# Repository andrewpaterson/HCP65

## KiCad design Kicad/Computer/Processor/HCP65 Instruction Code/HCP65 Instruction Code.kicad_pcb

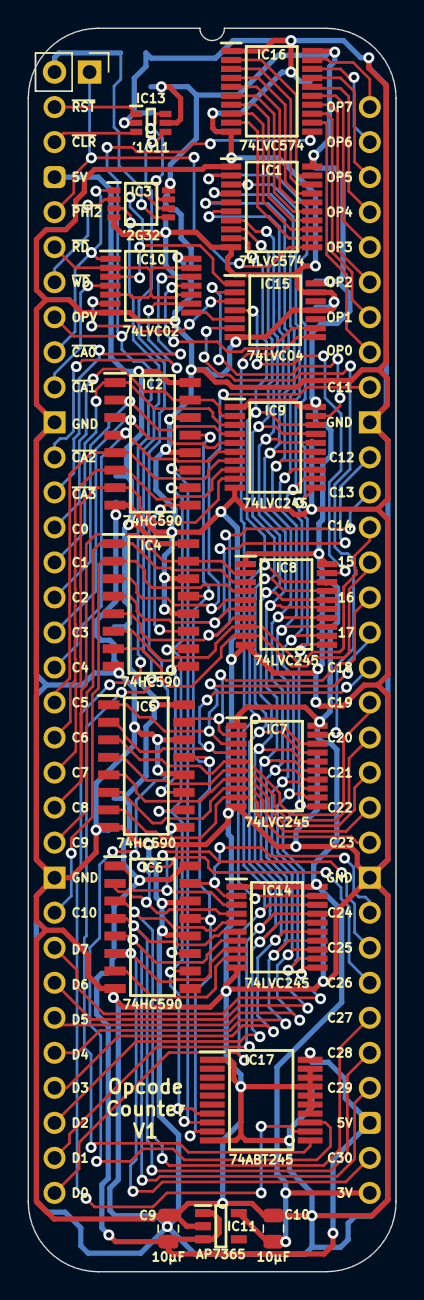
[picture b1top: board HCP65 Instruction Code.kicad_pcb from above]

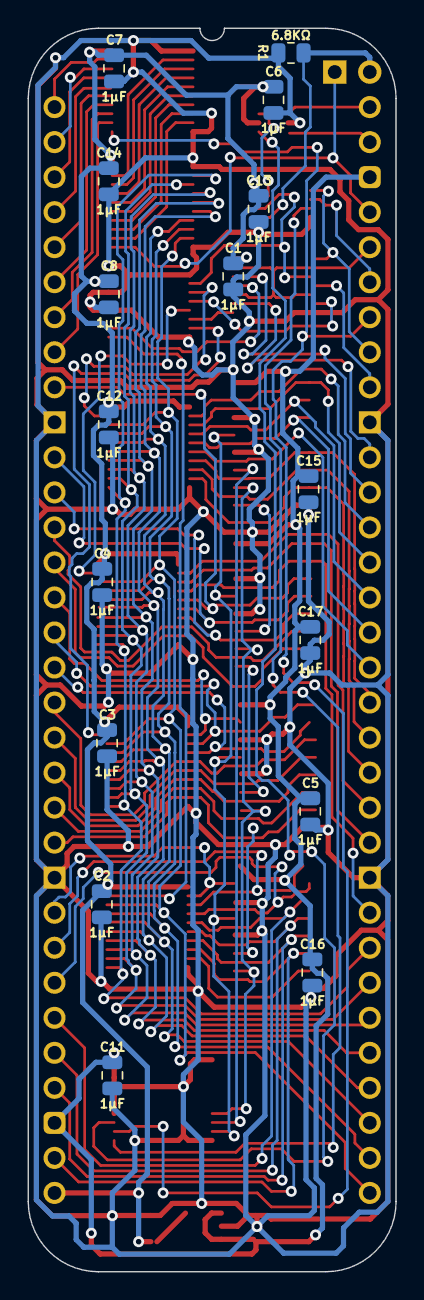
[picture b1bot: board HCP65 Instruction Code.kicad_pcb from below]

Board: 2 copper layers, 26.7 x 90.2 mm, 36 parts (16 on the bottom side), 87 nets.

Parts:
C1, C2, C3, C4, C5, C6, C7, C8, C11, C12, C13, C14, C15, C16, C17: 1μF; C_0805
C9, C10: 10μF; C_0805
IC1, IC16: 74LVC574APW,118; SOP65P640X110-20N
IC2, IC4, IC5, IC6: 74HC590D,118; SOIC127P600X175-16N
IC3: 74LVC2G32DP,125; SOP65P400X110-8N
IC7, IC8, IC9, IC14: 74LVC245AT20; SOP65P640X120-20N
IC10: 74LVC02APW,118; SOP65P640X110-14N
IC11: AP7365-33WG-7; SOT95P285X130-5N
IC13: 74LVC1G11GW-Q100H; SOP65P210X110-6N
IC15: 74LVC04APW,118; SOP65P640X110-14N
IC17: SN74ABT245BDBR; SOP65P780X200-20N
J2: Board 2x32 W22.86mm; DIP-64_Board_W22.86mm
J4: Conn_01x02_Pin; PinHeader_1x02_P2.54mm_Vertical
R1: 6.8KΩ; R_0805

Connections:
3.3V: C1.2, C2.2, C3.2, C4.2, C6.2, C7.2, C8.2, C10.1, C12.2, C13.2, C14.2, IC1.20 (3V), IC3.8 (VCC), IC7.1 (DIR), IC7.20 (3V), IC8.1 (DIR), IC8.20 (3V), IC9.1 (DIR), IC9.20 (3V), IC10.14 (3V), IC11.5 (3.3VOut), IC13.5 (3V), IC14.1 (DIR), IC14.20 (3V), IC15.14 (3V), IC16.20 (3V), J2.33
5V: C5.2, C9.1, C11.2, C15.2, C16.2, C17.2, IC2.16 (VCC), IC4.16 (VCC), IC5.16 (VCC), IC6.16 (VCC), IC11.1 (6VIn), IC11.3 (EN), IC17.20 (5V), J2.3, J2.35
/C31: IC6.7 (Q7), IC14.9 (A7)
/Opcode Valid_{5V}: IC2.11 (CPC), IC17.8 (A6)
/Q0: IC1.19 (Q0), IC16.2 (D0)
/Q1: IC1.18 (Q1), IC16.3 (D1)
/Q2: IC1.17 (Q2), IC16.4 (D2)
/Q3: IC1.16 (Q3), IC16.5 (D3)
/Q4: IC1.15 (Q4), IC16.6 (D4)
/Q5: IC1.14 (Q5), IC16.7 (D5)
/Q6: IC1.13 (Q6), IC16.8 (D6)
/Q7: IC1.12 (Q7), IC16.9 (D7)
/Read Count Access_{0T}: IC3.6 (2B), IC10.3 (1Y), IC15.1 (1A)
/Read Count Access_{0}: IC3.3 (2Y), IC17.11 (B7)
/Read Count Access_{1}: IC10.6 (2Y), IC15.3 (2A)
/Read Count Access_{2}: IC10.8 (3Y), IC15.5 (3A)
/Read Count Access_{3}: IC10.11 (4Y), IC15.9 (4A)
/Read Count_{5V}: IC2.13 (CPR), IC4.13 (CPR), IC5.13 (CPR), IC6.13 (CPR), IC17.9 (A7)
/~MRC: IC13.4 (Y), IC17.13 (B5)
/~MRC_{5V}: IC2.10 (~MRC), IC4.10 (~MRC), IC5.10 (~MRC), IC6.10 (~MRC), IC17.7 (A5)
/~Read Count Access_{0}: IC9.19 (~OE), IC15.2 (1Y)
/~Read Count Access_{1}: IC8.19 (~OE), IC15.4 (2Y)
/~Read Count Access_{2}: IC7.19 (~OE), IC15.6 (3Y)
/~Read Count Access_{3}: IC14.19 (~OE), IC15.8 (4Y)
/~Write Count: IC3.7 (1Y), IC13.6 (C)
C0: IC2.15 (Q0), IC9.2 (A0), J2.13
C1: IC2.1 (Q1), IC9.3 (A1), J2.14
C2: IC2.2 (Q2), IC9.4 (A2), J2.15
C3: IC2.3 (Q3), IC9.5 (A3), J2.16
C4: IC2.4 (Q4), IC9.6 (A4), J2.17
C5: IC2.5 (Q5), IC9.7 (A5), J2.18
C6: IC2.6 (Q6), IC9.8 (A6), J2.19
C7: IC2.7 (Q7), IC9.9 (A7), J2.20
C8: IC4.15 (Q0), IC8.2 (A0), J2.21
C9: IC4.1 (Q1), IC8.3 (A1), J2.22
C10: IC4.2 (Q2), IC8.4 (A2), J2.24
C11: IC4.3 (Q3), IC8.5 (A3), J2.56
C12: IC4.4 (Q4), IC8.6 (A4), J2.54
C13: IC4.5 (Q5), IC8.7 (A5), J2.53
C14: IC4.6 (Q6), IC8.8 (A6), J2.52
C15: IC4.7 (Q7), IC8.9 (A7), J2.51
C16: IC5.15 (Q0), IC7.2 (A0), J2.50
C17: IC5.1 (Q1), IC7.3 (A1), J2.49
C18: IC5.2 (Q2), IC7.4 (A2), J2.48
C19: IC5.3 (Q3), IC7.5 (A3), J2.47
C20: IC5.4 (Q4), IC7.6 (A4), J2.46
C21: IC5.5 (Q5), IC7.7 (A5), J2.45
C22: IC5.6 (Q6), IC7.8 (A6), J2.44
C23: IC5.7 (Q7), IC7.9 (A7), J2.43
C24: IC6.15 (Q0), IC14.2 (A0), J2.41
C25: IC6.1 (Q1), IC14.3 (A1), J2.40
C26: IC6.2 (Q2), IC14.4 (A2), J2.39
C27: IC6.3 (Q3), IC14.5 (A3), J2.38
C28: IC6.4 (Q4), IC14.6 (A4), J2.37
C29: IC6.5 (Q5), IC14.7 (A5), J2.36
C30: IC6.6 (Q6), IC14.8 (A6), J2.34
D0: IC1.9 (D7), IC7.18 (B0), IC8.18 (B0), IC9.18 (B0), IC14.18 (B0), J2.32
D1: IC1.8 (D6), IC7.17 (B1), IC8.17 (B1), IC9.17 (B1), IC14.17 (B1), J2.31
D2: IC1.7 (D5), IC7.16 (B2), IC8.16 (B2), IC9.16 (B2), IC14.16 (B2), J2.30
D3: IC1.6 (D4), IC7.15 (B3), IC8.15 (B3), IC9.15 (B3), IC14.15 (B3), J2.29
D4: IC1.5 (D3), IC7.14 (B4), IC8.14 (B4), IC9.14 (B4), IC14.14 (B4), J2.28
D5: IC1.4 (D2), IC7.13 (B5), IC8.13 (B5), IC9.13 (B5), IC14.13 (B5), J2.27
D6: IC1.3 (D1), IC7.12 (B6), IC8.12 (B6), IC9.12 (B6), IC14.12 (B6), J2.26
D7: IC1.2 (D0), IC7.11 (B7), IC8.11 (B7), IC9.11 (B7), IC14.11 (B7), J2.25
GND: C1.1, C2.1, C3.1, C4.1, C5.1, C6.1, C7.1, C8.1, C9.2, C10.2, C11.1, C12.1, C13.1, C14.1, C15.1, C16.1, C17.1, IC1.1 (~OE), IC1.10 (GND), IC2.8 (GND), IC2.12 (~CE), IC2.14 (~OE), IC3.4 (GND), IC4.8 (GND), IC4.12 (~CE), IC4.14 (~OE), IC5.8 (GND), IC5.12 (~CE), IC5.14 (~OE), IC6.8 (GND), IC6.12 (~CE), IC6.14 (~OE), IC7.10 (GND), IC8.10 (GND), IC9.10 (GND), IC10.7 (GND), IC11.2 (GND), IC13.2 (GND), IC14.10 (GND), IC15.7 (GND), IC15.11 (5A), IC15.13 (6A), IC16.1 (~OE), IC16.10 (GND), IC17.1 (DIR), IC17.10 (GND), IC17.14 (B4), IC17.15 (B3), IC17.16 (B2), IC17.17 (B1), IC17.18 (B0), IC17.19 (~OE), J2.10, J2.23, J2.42, J2.55, R1.2
unnamed: IC2.9 (~RCO), IC4.11 (CPC)
unnamed: IC3.5 (2A), J4.2, R1.1
unnamed: IC4.9 (~RCO), IC5.11 (CPC)
unnamed: IC5.9 (~RCO), IC6.11 (CPC)
OP0: IC16.12 (Q7), J2.57
OP1: IC16.13 (Q6), J2.58
OP2: IC16.14 (Q5), J2.59
OP3: IC16.15 (Q4), J2.60
OP4: IC16.16 (Q3), J2.61
OP5: IC16.17 (Q2), J2.62
OP6: IC16.18 (Q1), J2.63
OP7: IC16.19 (Q0), J2.64
Opcode Valid: IC16.11 (CP), IC17.12 (B6), J2.7
~Clear Counter: IC13.3 (B), J2.2
~Count Access_{0}: IC3.1 (1A), IC10.1 (1A), J2.8
~Count Access_{1}: IC10.4 (2A), J2.9
~Count Access_{2}: IC10.9 (3A), J2.11
~Count Access_{3}: IC10.12 (4A), J2.12
~PHI2: IC1.11 (CP), J2.4, J4.1
~RD: IC10.2 (1B), IC10.5 (2B), IC10.10 (3B), IC10.13 (4B), J2.5
~Reset: IC13.1 (A), J2.1
~WD: IC3.2 (1B), J2.6

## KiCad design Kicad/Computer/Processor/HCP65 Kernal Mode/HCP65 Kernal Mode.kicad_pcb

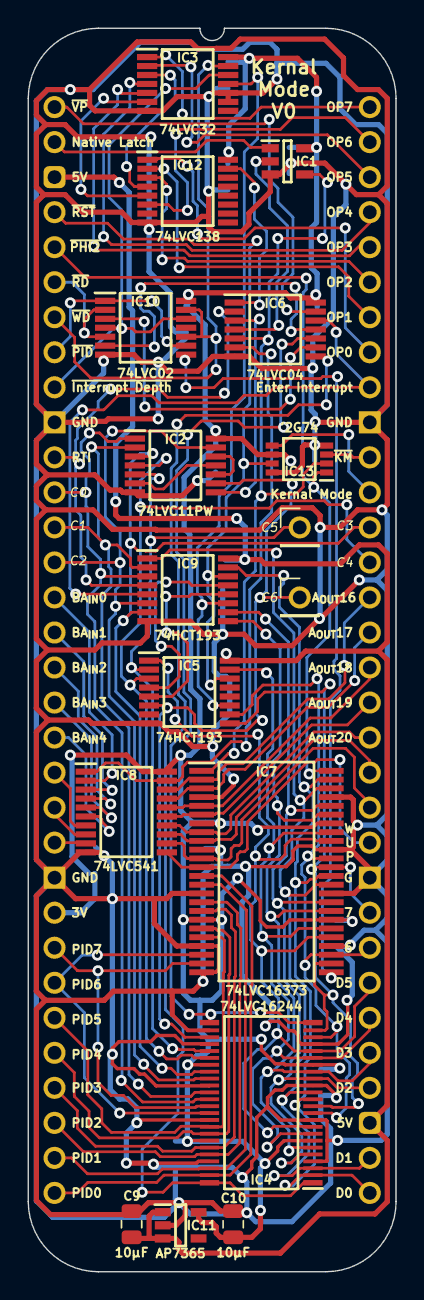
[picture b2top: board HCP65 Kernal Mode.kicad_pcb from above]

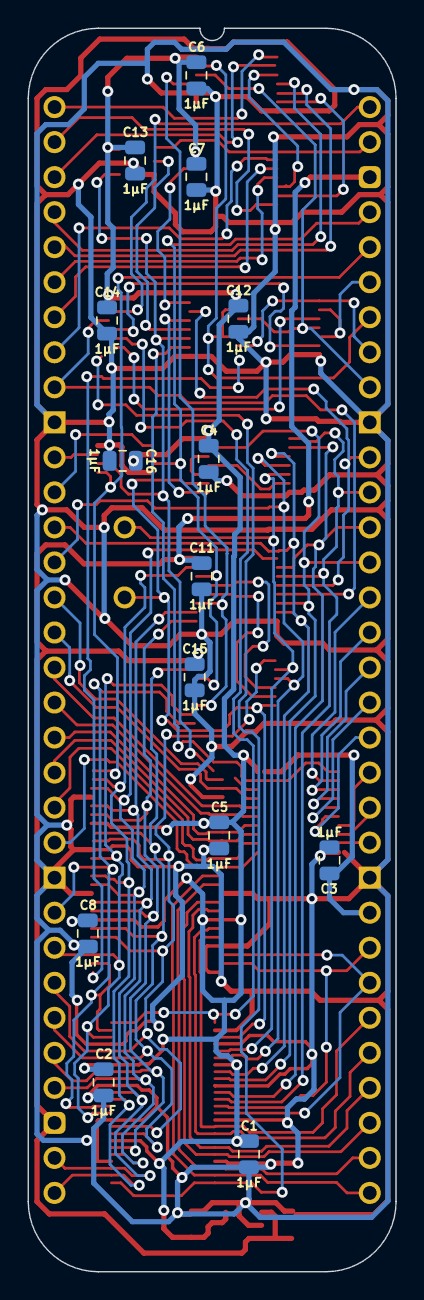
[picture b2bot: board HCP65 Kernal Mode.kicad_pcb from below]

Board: 2 copper layers, 26.7 x 90.2 mm, 32 parts (14 on the bottom side), 79 nets.

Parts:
C1, C2, C3, C4, C5, C6, C7, C8, C11, C12, C13, C14, C15, C16: 1μF; C_0805
C9, C10: 10μF; C_0805
IC1: 74LVC1G02GV,125; SOT95P275X110-5N
IC2: 74LVC11PW,112; SOP65P640X110-14N
IC3: 74LVC32APW,118; SOP65P640X110-14N
IC4: 74LVC16244ADGG,112; 74LVC16244ADGG112
IC5, IC9: 74HCT193PW,118; SOP65P640X110-16N
IC6: 74LVC04APW,118; SOP65P640X110-14N
IC7: 74LVC16373ADL,118; SOP64P1025X280-48N
IC8: 74LVC541APW,118; SOP65P640X110-20N
IC10: 74LVC02APW,118; SOP65P640X110-14N
IC11: AP7365-33WG-7; SOT95P285X130-5N
IC12: 74LVC138APW-Q100J; SOP65P640X110-16N
IC13: 74LVC2G74DP,125; SOP65P400X110-8N
J2: Board 2x32 W22.86mm; DIP-64_Board_W22.86mm
TP1, TP2: TestPoint; PinHeader_1x01_P2.54mm_Vertical

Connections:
3.3V: C1.2, C2.2, C3.2, C4.2, C5.2, C6.2, C7.2, C8.2, C10.1, C12.2, C13.2, C14.2, C16.2, IC1.5 (3V), IC2.14 (3V), IC3.14 (3V), IC4.7 (3V), IC4.18 (3V), IC4.31 (3V), IC4.42 (3V), IC6.14 (3V), IC7.7 (3V), IC7.18 (3V), IC7.31 (3V), IC7.42 (3V), IC8.20 (3V), IC10.14 (3V), IC11.5 (3.3VOut), IC12.16 (3V), IC13.6 (~RD), J2.24
5V: C9.1, C11.2, C15.2, IC5.16 (5V), IC9.16 (5V), IC11.1 (6VIn), IC11.3 (EN), J2.3, J2.35
/C0·C1·C2: IC2.10 (3B), IC2.12 (1Y)
/C3·C4·C5: IC2.6 (2Y), IC2.11 (3C)
/Kernal Mode: IC1.4 (Y), IC6.5 (3A), IC7.1 (1~OE), IC13.2 (D)
/Kernal Mode_{ PART}: IC2.8 (3Y), IC6.3 (2A)
/OP3+OP4: IC3.6 (2Y), IC12.5 (~E2)
/OP5+OP7: IC3.3 (1Y), IC12.4 (~E1)
/Read Interrupt Depth: IC6.11 (5A), IC10.6 (2Y)
/Read Process ID: IC6.9 (4A), IC10.3 (1Y)
/Write Process ID: IC7.25 (2LE), IC10.8 (3Y)
/~Kernal Mode: IC6.6 (3Y), IC8.1 (~OE1), IC8.19 (~OE2)
/~Kernal Mode_{ PART}: IC1.2 (A), IC6.4 (2Y)
/~RTI: IC6.1 (1A), IC12.15 (~Y0)
/~Read Interrupt Depth: IC4.24 (4~OE), IC4.25 (3~OE), IC6.10 (5Y)
/~Read Process ID: IC4.1 (1~OE), IC4.48 (2~OE), IC6.8 (4Y)
/~TCD: IC5.4 (CPD), IC9.13 (~TCD)
/~TCU: IC5.5 (CPU), IC9.12 (~TCU)
/~Write Interrupt Depth: IC3.11 (4Y), IC5.11 (~PL), IC9.11 (~PL)
A_{OUT}16: IC7.2 (1Q0), IC8.18 (Y0), J2.50
A_{OUT}17: IC7.3 (1Q1), IC8.17 (Y1), J2.49
A_{OUT}18: IC7.5 (1Q2), IC8.16 (Y2), J2.48
A_{OUT}19: IC7.6 (1Q3), IC8.15 (Y3), J2.47
A_{OUT}20: IC7.8 (1Q4), IC8.14 (Y4), J2.46
A_{OUT}21: IC7.9 (1Q5), IC8.13 (Y5), J2.45
A_{OUT}22: IC7.11 (1Q6), IC8.12 (Y6), J2.44
A_{OUT}23: IC7.12 (1Q7), IC8.11 (Y7), J2.43
BA_{IN}0: IC8.2 (A0), J2.15
BA_{IN}1: IC8.3 (A1), J2.16
BA_{IN}2: IC8.4 (A2), J2.17
BA_{IN}3: IC8.5 (A3), J2.18
BA_{IN}4: IC8.6 (A4), J2.19
BA_{IN}5: IC8.7 (A5), J2.20
BA_{IN}6: IC8.8 (A6), J2.21
BA_{IN}7: IC8.9 (A7), J2.22
C0: IC2.1 (1A), IC4.36 (3A0), IC9.3 (Q0), J2.12
C1: IC2.2 (1B), IC4.35 (3A1), IC9.2 (Q1), J2.13
C2: IC2.13 (1C), IC4.33 (3A2), IC9.6 (Q2), J2.14
C3: IC2.3 (2A), IC4.32 (3A3), IC9.7 (Q3), J2.52
C4: IC2.4 (2B), IC4.30 (4A0), IC5.3 (Q0), J2.51
C5: IC2.5 (2C), IC4.29 (4A1), IC5.2 (Q1), TP2.1 (1_1)
C6: IC2.9 (3A), IC4.27 (4A2), IC5.6 (Q2), TP1.1 (1_1)
D0: IC4.2 (1Y0), IC4.13 (3Y0), IC7.36 (2D0), IC7.47 (1D0), IC9.15 (D0), J2.33
D1: IC4.3 (1Y1), IC4.14 (3Y1), IC7.35 (2D1), IC7.46 (1D1), IC9.1 (D1), J2.34
D2: IC4.5 (1Y2), IC4.16 (3Y2), IC7.33 (2D2), IC7.44 (1D2), IC9.10 (D2), J2.36
D3: IC4.6 (1Y3), IC4.17 (3Y3), IC7.32 (2D3), IC7.43 (1D3), IC9.9 (D3), J2.37
D4: IC4.8 (2Y0), IC4.19 (4Y0), IC5.15 (D0), IC7.30 (2D4), IC7.41 (1D4), J2.38
D5: IC4.9 (2Y1), IC4.20 (4Y1), IC5.1 (D1), IC7.29 (2D5), IC7.40 (1D5), J2.39
D6: IC4.11 (2Y2), IC4.22 (4Y2), IC5.10 (D2), IC7.27 (2D6), IC7.38 (1D6), J2.40
D7: IC4.12 (2Y3), IC4.23 (4Y3), IC5.9 (D3), IC7.26 (2D7), IC7.37 (1D7), J2.41
Enter Interrupt: IC6.12 (6Y), IC9.5 (CPU), J2.56
GND: C1.1, C2.1, C3.1, C4.1, C5.1, C6.1, C7.1, C8.1, C9.2, C10.2, C11.1, C12.1, C13.1, C14.1, C15.1, C16.1, IC1.3 (GND), IC2.7 (GND), IC3.7 (GND), IC3.9 (3A), IC3.10 (3B), IC4.4 (GND), IC4.10 (GND), IC4.15 (GND), IC4.21 (GND), IC4.26 (4A3), IC4.28 (GND), IC4.34 (GND), IC4.39 (GND), IC4.45 (GND), IC5.8 (GND), IC6.7 (GND), IC7.4 (GND), IC7.10 (GND), IC7.15 (GND), IC7.21 (GND), IC7.24 (2~OE), IC7.28 (GND), IC7.34 (GND), IC7.39 (GND), IC7.45 (GND), IC8.10 (GND), IC9.8 (GND), IC10.7 (GND), IC11.2 (GND), IC12.8 (GND), IC13.4 (GND), IC13.8 (3V), J2.10, J2.23, J2.42, J2.55
Kernal Mode OUT: IC13.5 (Q), J2.53
Native Latch: IC1.1 (B), J2.2
OP0: IC12.1 (A0), J2.57
OP1: IC12.2 (A1), J2.58
OP2: IC12.3 (A2), J2.59
OP3: IC3.5 (2B), J2.60
OP4: IC3.4 (2A), J2.61
OP5: IC3.2 (1B), J2.62
OP6: IC12.6 (E3), J2.63
OP7: IC3.1 (1A), J2.64
PID0: IC4.47 (1A0), IC7.13 (2Q0), J2.32
PID1: IC4.46 (1A1), IC7.14 (2Q1), J2.31
PID2: IC4.44 (1A2), IC7.16 (2Q2), J2.30
PID3: IC4.43 (1A3), IC7.17 (2Q3), J2.29
PID4: IC4.41 (2A0), IC7.19 (2Q4), J2.28
PID5: IC4.40 (2A1), IC7.20 (2Q5), J2.27
PID6: IC4.38 (2A2), IC7.22 (2Q6), J2.26
PID7: IC4.37 (2A3), IC7.23 (2Q7), J2.25
RTI: IC6.2 (1Y), IC9.4 (CPD), J2.11
~Interrupt Depth: IC3.12 (4A), IC10.4 (2A), IC10.12 (4A), J2.9
~Kernal Mode OUT: IC13.3 (~Q), J2.54
~PHI2: IC7.48 (1LE), IC13.1 (CP), J2.5
~Process ID: IC10.1 (1A), IC10.9 (3A), J2.8
~RD: IC10.2 (1B), IC10.5 (2B), J2.6
~Reset: IC5.14 (MR), IC9.14 (MR), IC13.7 (~SD), J2.4
~VP: IC6.13 (6A), J2.1
~WD: IC3.13 (4B), IC10.10 (3B), IC10.13 (4B), J2.7

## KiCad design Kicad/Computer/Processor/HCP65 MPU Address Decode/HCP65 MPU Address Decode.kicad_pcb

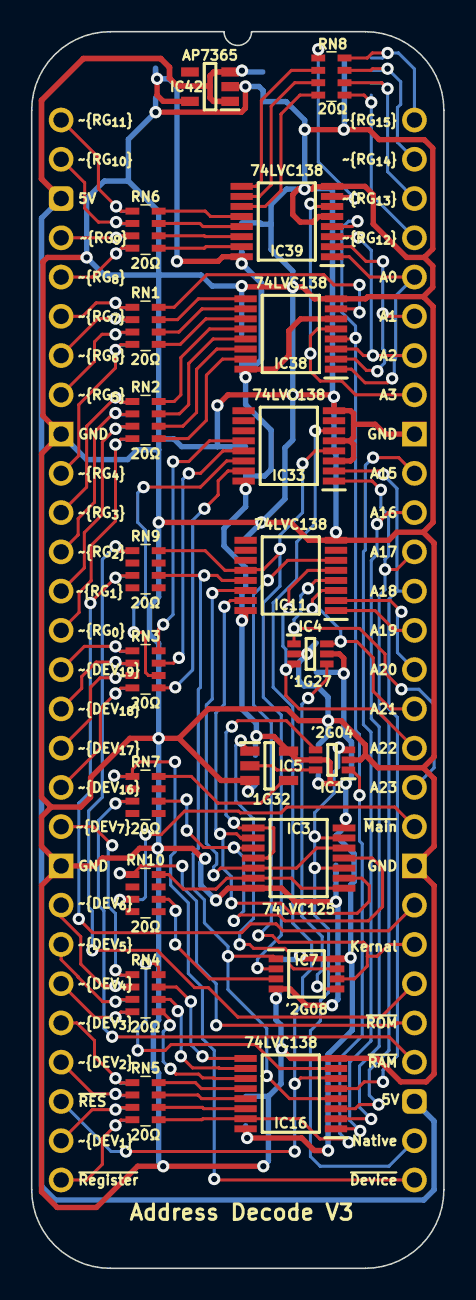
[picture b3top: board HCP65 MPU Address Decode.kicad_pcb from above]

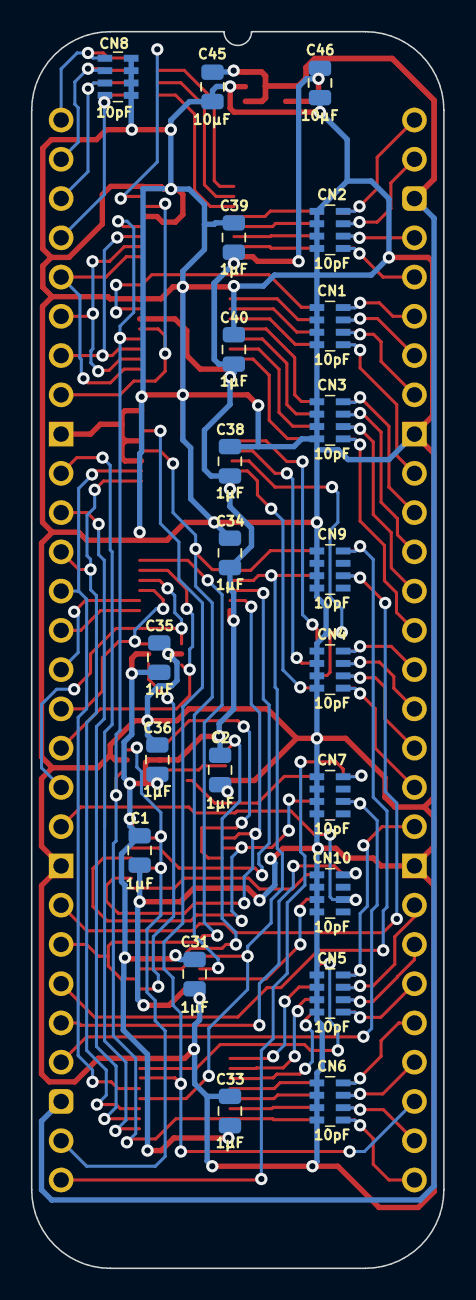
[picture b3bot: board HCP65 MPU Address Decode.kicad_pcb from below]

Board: 2 copper layers, 26.7 x 80.0 mm, 44 parts (22 on the bottom side), 93 nets.

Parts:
C1, C2, C31, C33, C34, C35, C36, C38, C39, C40: 1μF; C_0805
C45, C46: 10μF; C_0805
CN1, CN2, CN3, CN4, CN5, CN6, CN7, CN8, CN9, CN10: CA0612KRX7R9BB100
IC1: 74LVC2G04GW-Q100H; SOP65P210X110-6N
IC3: 74LVC125APW-Q100J; SOP65P640X110-14N
IC4: 74LVC1G27GW,125; SOP65P210X110-6N
IC5: 74LVC1G32GV,125; SOT95P275X110-5N
IC7: 74LVC2G08DP-Q100H; SOP65P400X110-8N
IC11, IC16, IC33, IC38, IC39: 74LVC138APW-Q100J; SOP65P640X110-16N
IC42: AP7365-33WG-7; SOT95P285X130-5N
J2: Board 2x28 W22.86mm; DIP-56_Board_W22.86mm
RN1, RN2, RN3, RN4, RN5, RN6, RN7, RN8, RN9, RN10: CAY16-200J4LF; CAY16-F4

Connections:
5V: C45.1, IC42.1 (6VIn), IC42.3 (EN), J2.3, J2.31
/3.3V: C1.1, C2.1, C31.1, C33.1, C34.1, C35.1, C36.1, C38.1, C39.1, C40.1, C46.1, IC1.5 (3V), IC3.14 (3V), IC4.5 (3V), IC5.5 (3V), IC7.8 (3V), IC11.16 (3V), IC16.16 (3V), IC33.16 (3V), IC38.6 (E3), IC38.16 (3V), IC39.16 (3V), IC42.5 (3.3VOut)
/Registers: IC1.6 (1Y), IC5.2 (A)
/~A21+A22+A23: IC4.4 (Y), IC7.5 (2A)
/~Device1_{I}: IC16.14 (~Y1), RN5.6 (R3)
/~Device2_{I}: IC16.13 (~Y2), RN5.7 (R2)
/~Device3_{I}: IC16.12 (~Y3), RN5.8 (R1)
/~Device4_{I}: IC16.11 (~Y4), RN4.5 (R4)
/~Device5_{I}: IC16.10 (~Y5), RN4.6 (R3)
/~Device6_{I}: IC16.9 (~Y6), RN4.7 (R2)
/~Device7_{I}: IC16.7 (~Y7), RN4.8 (R1)
/~Device16_{I}: IC33.15 (~Y0), RN3.5 (R4)
/~Device17_{I}: IC33.14 (~Y1), RN3.6 (R3)
/~Device18_{I}: IC33.13 (~Y2), RN3.7 (R2)
/~Device19_{I}: IC33.12 (~Y3), RN3.8 (R1)
/~Device Group 32K_{I}: IC7.1 (1A), IC11.13 (~Y2), IC16.4 (~E1), RN9.6 (R3)
/~Device Group 128K_{I}: IC7.2 (1B), IC11.12 (~Y3), IC33.4 (~E1), RN9.8 (R1)
/~Device Group: IC5.1 (B), IC7.7 (1Y)
/~Devices_{I}: IC5.4 (Y), RN7.8 (R1)
/~Main Memory_{I}: IC7.3 (2Y), RN10.6 (R3)
/~RAM Swap: IC1.4 (2Y), IC3.1 (~1OE), IC3.4 (~2OE)
/~RAM_{II}: IC3.2 (1A), IC3.9 (3A), IC11.15 (~Y0)
/~RAM_{I}: IC3.3 (1Y), IC3.11 (4Y), RN7.6 (R3)
/~ROM_{II}: IC3.5 (2A), IC3.12 (4A), IC11.14 (~Y1)
/~ROM_{I}: IC3.6 (2Y), IC3.8 (3Y), RN10.8 (R1)
/~Register0_{I}: IC38.15 (~Y0), RN2.5 (R4)
/~Register1_{I}: IC38.14 (~Y1), RN2.6 (R3)
/~Register2_{I}: IC38.13 (~Y2), RN2.7 (R2)
/~Register3_{I}: IC38.12 (~Y3), RN2.8 (R1)
/~Register4_{I}: IC38.11 (~Y4), RN1.5 (R4)
/~Register5_{I}: IC38.10 (~Y5), RN1.6 (R3)
/~Register6_{I}: IC38.9 (~Y6), RN1.7 (R2)
/~Register7_{I}: IC38.7 (~Y7), RN1.8 (R1)
/~Register8_{I}: IC39.15 (~Y0), RN6.5 (R4)
/~Register9_{I}: IC39.14 (~Y1), RN6.6 (R3)
/~Register10_{I}: IC39.13 (~Y2), RN6.7 (R2)
/~Register11_{I}: IC39.12 (~Y3), RN6.8 (R1)
/~Register12_{I}: IC39.11 (~Y4), RN8.8 (R1)
/~Register13_{I}: IC39.10 (~Y5), RN8.7 (R2)
/~Register14_{I}: IC39.9 (~Y6), RN8.6 (R3)
/~Register15_{I}: IC39.7 (~Y7), RN8.5 (R4)
/~Registers_{I}: IC1.1 (1A), IC16.15 (~Y0), IC38.4 (~E1), IC39.4 (~E1), RN5.5 (R4)
A0: IC38.1 (A0), IC39.1 (A0), J2.52
A1: IC38.2 (A1), IC39.2 (A1), J2.51
A2: IC38.3 (A2), IC39.3 (A2), J2.50
A3: IC38.5 (~E2), IC39.6 (E3), J2.49
A15: IC16.1 (A0), J2.47
A16: IC16.2 (A1), J2.46
A17: IC16.3 (A2), IC33.1 (A0), J2.45
A18: IC16.5 (~E2), IC33.2 (A1), J2.44
A19: IC11.1 (A0), J2.43
A20: IC11.2 (A1), J2.42
A21: IC4.6 (C), IC11.3 (A2), J2.41
A22: IC4.3 (B), IC11.5 (~E2), J2.40
A23: IC4.1 (A), IC11.4 (~E1), J2.39
GND: C1.2, C2.2, C31.2, C33.2, C34.2, C35.2, C36.2, C38.2, C39.2, C40.2, C45.2, C46.2, CN1.5, CN1.6, CN1.7, CN1.8, CN2.5, CN2.6, CN2.7, CN2.8, CN3.5, CN3.6, CN3.7, CN3.8, CN4.5, CN4.6, CN4.7, CN4.8, CN5.5, CN5.6, CN5.7, CN5.8, CN6.5, CN6.6, CN6.7, CN6.8, CN7.5, CN7.6, CN7.7, CN7.8, CN8.5, CN8.6, CN8.7, CN8.8, CN9.5, CN9.6, CN9.7, CN9.8, CN10.5, CN10.6, CN10.7, CN10.8, IC1.2 (GND), IC3.7 (GND), IC4.2 (GND), IC5.3 (GND), IC7.4 (GND), IC11.8 (GND), IC16.8 (GND), IC33.3 (A2), IC33.5 (~E2), IC33.8 (GND), IC38.8 (GND), IC39.5 (~E2), IC39.8 (GND), IC42.2 (GND), J2.9, J2.20, J2.37, J2.48
Kernal Mode: IC7.6 (2B), IC11.6 (E3), J2.35
RAM Swap: IC1.3 (2A), IC3.10 (~3OE), IC3.13 (~4OE), J2.30
~Device1: CN6.2, J2.27, RN5.3 (R3)
~Device2: CN6.3, J2.25, RN5.2 (R2)
~Device3: CN6.4, J2.24, RN5.1 (R1)
~Device4: CN5.1, J2.23, RN4.4 (R4)
~Device5: CN5.2, J2.22, RN4.3 (R3)
~Device6: CN5.3, J2.21, RN4.2 (R2)
~Device7: CN5.4, J2.19, RN4.1 (R1)
~Device16: CN4.1, J2.18, RN3.4 (R4)
~Device17: CN4.2, J2.17, RN3.3 (R3)
~Device18: CN4.3, J2.16, RN3.2 (R2)
~Device19: CN4.4, J2.15, RN3.1 (R1)
~Device Group 32K: CN9.2, J2.36, RN9.3 (R3)
~Device Group 128K: CN9.4, J2.34, RN9.1 (R1)
~Devices: CN7.4, J2.29, RN7.1 (R1)
~Main Memory: CN10.2, J2.38, RN10.3 (R3)
~RAM: CN7.2, J2.32, RN7.3 (R3)
~ROM: CN10.4, J2.33, RN10.1 (R1)
~Register0: CN3.1, J2.14, RN2.4 (R4)
~Register1: CN3.2, J2.13, RN2.3 (R3)
~Register2: CN3.3, J2.12, RN2.2 (R2)
~Register3: CN3.4, J2.11, RN2.1 (R1)
~Register4: CN1.1, J2.10, RN1.4 (R4)
~Register5: CN1.2, J2.8, RN1.3 (R3)
~Register6: CN1.3, J2.7, RN1.2 (R2)
~Register7: CN1.4, J2.6, RN1.1 (R1)
~Register8: CN2.1, J2.5, RN6.4 (R4)
~Register9: CN2.2, J2.4, RN6.3 (R3)
~Register10: CN2.3, J2.2, RN6.2 (R2)
~Register11: CN2.4, J2.1, RN6.1 (R1)
~Register12: CN8.4, J2.53, RN8.1 (R1)
~Register13: CN8.3, J2.54, RN8.2 (R2)
~Register14: CN8.2, J2.55, RN8.3 (R3)
~Register15: CN8.1, J2.56, RN8.4 (R4)
~Registers: CN6.1, J2.28, RN5.4 (R4)
~Reset: IC16.6 (E3), IC33.6 (E3), J2.26

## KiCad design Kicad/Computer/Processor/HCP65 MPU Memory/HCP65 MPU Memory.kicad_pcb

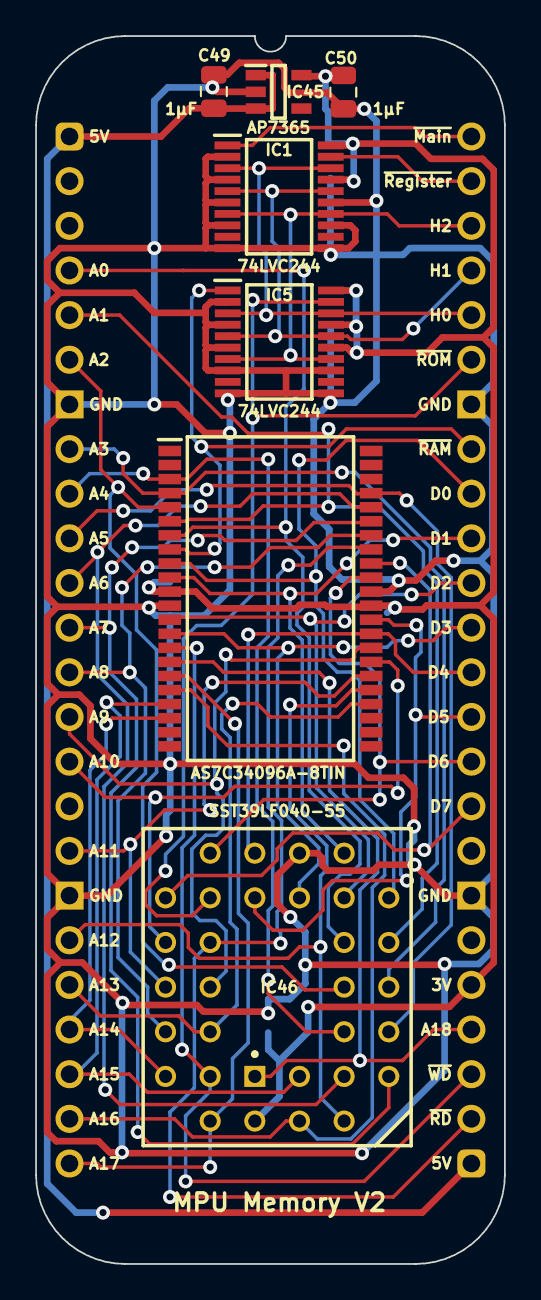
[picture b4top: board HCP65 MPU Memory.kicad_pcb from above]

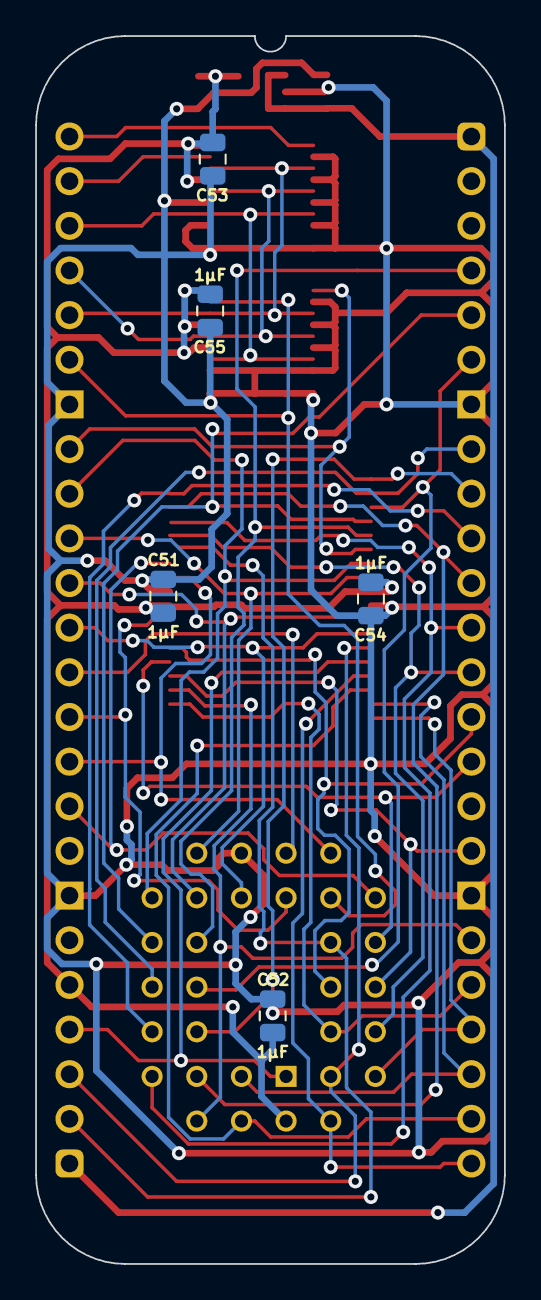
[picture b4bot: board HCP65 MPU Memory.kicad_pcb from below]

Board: 2 copper layers, 26.7 x 69.9 mm, 13 parts (5 on the bottom side), 39 nets.

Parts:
C49, C50, C51, C52, C53, C54, C55: 1μF; C_0805
IC1, IC5: 74LVC244APW,118; SOP65P640X110-20N
IC25: AS7C34096A-8TIN; SOP80P1176X120-44N
IC45: AP7365-33WG-7; SOT95P285X130-5N
IC46: SST39LF040-55-4C-NHE; 5408803224008
J8: Board 2x24 W22.86mm; DIP-48_Board_W22.86mm

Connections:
3.3V: C50.1, C51.1, C52.1, C53.1, C54.1, C55.1, IC1.17 (2A0), IC1.20 (3V), IC5.15 (2A1), IC5.17 (2A0), IC5.20 (3V), IC25.11 (3V), IC25.33 (3V), IC45.5 (3.3VOut), IC46.32 (3V), J8.29
5V: C49.1, IC45.1 (6VIn), IC45.3 (EN), J8.1, J8.25
A0: IC25.7 (A0), IC46.12 (A0), J8.4
A1: IC25.6 (A1), IC46.11 (A1), J8.5
A2: IC25.5 (A2), IC46.10 (A2), J8.6
A3: IC25.4 (A3), IC46.9 (A3), J8.8
A4: IC25.3 (A4), IC46.8 (A4), J8.9
A5: IC25.41 (A5), IC46.7 (A5), J8.10
A6: IC25.40 (A6), IC46.6 (A6), J8.11
A7: IC25.39 (A7), IC46.5 (A7), J8.12
A8: IC25.38 (A8), IC46.27 (A8), J8.13
A9: IC25.30 (A9), IC46.26 (A9), J8.14
A10: IC25.29 (A10), IC46.23 (A10), J8.15
A11: IC25.28 (A11), IC46.25 (A11), J8.17
A12: IC25.27 (A12), IC46.4 (A12), J8.19
A13: IC25.26 (A13), IC46.28 (A13), J8.20
A14: IC25.20 (A14), IC46.29 (A14), J8.21
A15: IC25.19 (A15), IC46.3 (A15), J8.22
A16: IC25.18 (A16), IC46.2 (A16), J8.23
A17: IC25.17 (A17), IC46.30 (A17), J8.24
A18: IC25.16 (A18), IC46.1 (A18), J8.28
D0: IC25.9 (D0), IC46.13 (DQ0), J8.40
D1: IC25.10 (D1), IC46.14 (DQ1), J8.39
D2: IC25.13 (D2), IC46.15 (DQ2), J8.38
D3: IC25.14 (D3), IC46.17 (DQ3), J8.37
D4: IC25.31 (D4), IC46.18 (DQ4), J8.36
D5: IC25.32 (D5), IC46.19 (DQ5), J8.35
D6: IC25.35 (D6), IC46.20 (DQ6), J8.34
D7: IC25.36 (D7), IC46.21 (DQ7), J8.33
GND: C49.2, C50.2, C51.2, C52.2, C53.2, C54.2, C55.2, IC1.2 (1A0), IC1.4 (1A1), IC1.6 (1A2), IC1.8 (1A3), IC1.10 (GND), IC1.11 (2A3), IC1.13 (2A2), IC1.15 (2A1), IC5.2 (1A0), IC5.4 (1A1), IC5.6 (1A2), IC5.8 (1A3), IC5.10 (GND), IC5.11 (2A3), IC5.13 (2A2), IC25.12 (GND), IC25.34 (GND), IC45.2 (GND), IC46.16 (GND), J8.7, J8.18, J8.31, J8.42
H0: IC1.3 (2Y0), IC1.18 (1Y0), IC5.3 (2Y0), IC5.18 (1Y0), J8.44
H1: IC1.5 (2Y1), IC1.16 (1Y1), IC5.5 (2Y1), IC5.16 (1Y1), J8.45
H2: IC1.7 (2Y2), IC1.14 (1Y2), IC5.7 (2Y2), IC5.14 (1Y2), J8.46
~Main: IC1.1 (~1OE), J8.48
~RAM: IC5.1 (~1OE), IC25.8 (~CE), J8.41
~RD: IC25.37 (~OE), IC46.24 (~OE), J8.26
~ROM: IC5.19 (~2OE), IC46.22 (~CE), J8.43
~Register: IC1.19 (~2OE), J8.47
~WD: IC25.15 (~WE), IC46.31 (~WE), J8.27

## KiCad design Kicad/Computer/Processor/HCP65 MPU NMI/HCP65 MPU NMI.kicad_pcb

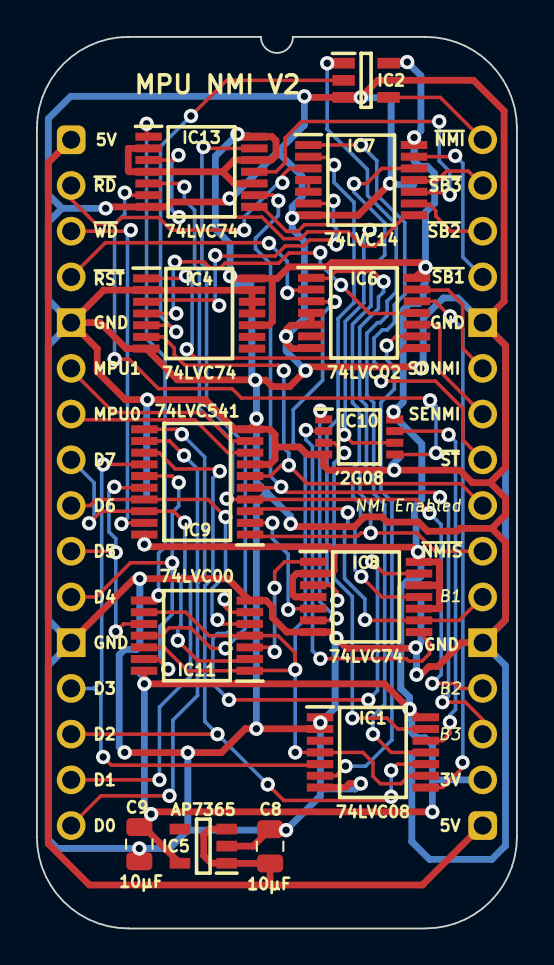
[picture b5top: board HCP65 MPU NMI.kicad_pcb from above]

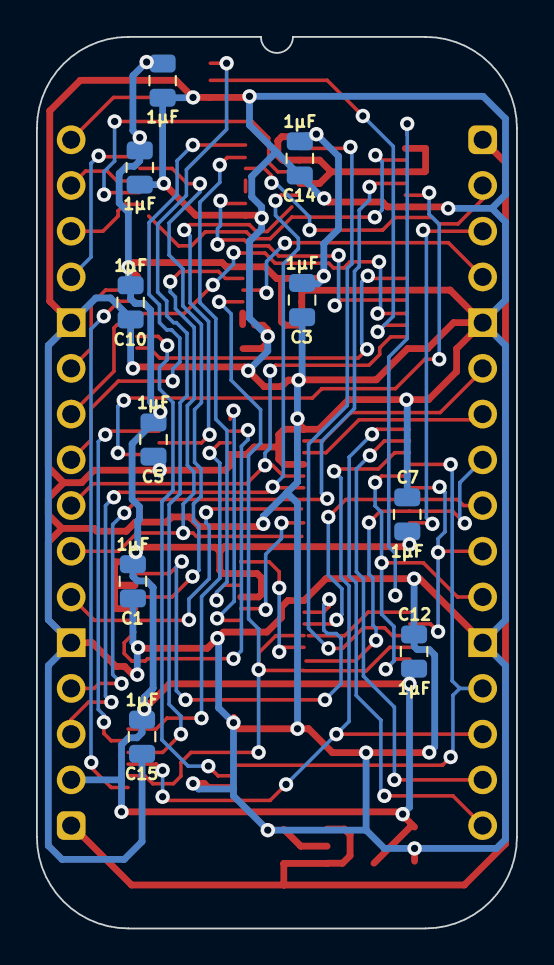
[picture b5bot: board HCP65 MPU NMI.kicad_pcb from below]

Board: 2 copper layers, 26.7 x 49.5 mm, 24 parts (10 on the bottom side), 52 nets.

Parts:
C1, C2, C3, C5, C6, C7, C10, C12, C14, C15: 1μF; C_0805
C8, C9: 10μF; C_0805
IC1: 74LVC08APW,112; SOP65P640X110-14N
IC2: 74LVC1G32GV,125; SOT95P275X110-5N
IC4, IC8, IC13: 74LVC74APW,118; SOP65P640X110-14N
IC5: AP7365-33WG-7; SOT95P285X130-5N
IC6: 74LVC02APW,118; SOP65P640X110-14N
IC7: 74LVC14APW,118; SOP65P640X110-14N
IC9: 74LVC541APW,118; SOP65P640X110-20N
IC10: 74LVC2G08DP-Q100H; SOP65P400X110-8N
IC11: 74LVC00APW,112; SOP65P640X110-14N
J2: Board 2x16 W22.86mm; DIP-32_Board_W22.86mm

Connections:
3.3V: C1.1, C2.1, C3.1, C5.1, C6.1, C7.1, C9.1, C10.1, C12.1, C14.1, C15.1, IC1.14 (3V), IC2.5 (3V), IC4.10 (~2SD), IC4.14 (3V), IC5.5 (3.3VOut), IC6.14 (3V), IC7.14 (3V), IC8.2 (1D), IC8.4 (~1SD), IC8.10 (~2SD), IC8.12 (2D), IC8.14 (3V), IC9.20 (3V), IC10.8 (3V), IC11.14 (3V), IC13.2 (1D), IC13.4 (~1SD), IC13.10 (~2SD), IC13.12 (2D), IC13.14 (3V), J2.18
5V: C8.1, IC5.1 (6VIn), IC5.3 (EN), J2.1, J2.17
/NMI Mask: IC2.2 (A), IC4.5 (1Q)
/NMI State·WD: IC1.4 (2A), IC1.9 (3A), IC6.3 (1Y), IC11.1 (1A), IC11.4 (2A), IC11.9 (3A), IC11.12 (4A)
/Reset: IC7.4 (2Y), IC7.5 (3A)
/Set Break_{1}: IC7.12 (6Y), IC8.11 (2CP)
/Set Break_{2}: IC7.8 (4Y), IC13.3 (1CP)
/Set Break_{3}: IC7.10 (5Y), IC13.11 (2CP)
/Set Timer: IC7.2 (1Y), IC8.3 (1CP)
/Timer: IC8.5 (1Q), IC9.2 (A0)
/Write Disable NMI: IC1.8 (3Y), IC6.12 (4A)
/Write Enable NMI: IC1.6 (2Y), IC6.9 (3A)
/~Break_{1}: IC8.8 (~2Q), IC10.2 (1B)
/~Break_{2}: IC10.5 (2A), IC13.6 (~1Q)
/~Break_{2}·~Break_{3}: IC1.13 (4B), IC10.3 (2Y)
/~Break_{3}: IC10.6 (2B), IC13.8 (~2Q)
/~Clear Break_{1}: IC8.13 (~2RD), IC11.6 (2Y)
/~Clear Break_{2}: IC11.8 (3Y), IC13.1 (~1RD)
/~Clear Break_{3}: IC11.11 (4Y), IC13.13 (~2RD)
/~Clear Timer: IC8.1 (~1RD), IC11.3 (1Y)
/~Disable NMI: IC4.4 (~1SD), IC6.11 (4Y)
/~Enable NMI: IC4.1 (~1RD), IC6.8 (3Y)
/~Reset_{2}: IC4.3 (1CP), IC7.6 (3Y)
/~Timer: IC8.6 (~1Q), IC10.1 (1A)
/~Timer·~Break_{1}: IC1.12 (4A), IC10.7 (1Y)
/~Unmasked NMI: IC1.11 (4Y), IC2.1 (B)
Break_{1}: IC8.9 (2Q), IC9.3 (A1), J2.22
Break_{2}: IC9.4 (A2), IC13.5 (1Q), J2.20
Break_{3}: IC9.5 (A3), IC13.9 (2Q), J2.19
D0: IC9.18 (Y0), IC11.2 (1B), J2.8
D1: IC9.17 (Y1), IC11.5 (2B), J2.9
D2: IC9.16 (Y2), IC11.10 (3B), J2.10
D3: IC9.15 (Y3), IC11.13 (4B), J2.11
D4: IC1.5 (2B), IC9.14 (Y4), J2.13
D5: IC1.10 (3B), IC9.13 (Y5), J2.14
D6: IC9.12 (Y6), J2.15
D7: IC9.11 (Y7), J2.16
GND: C1.2, C2.2, C3.2, C5.2, C6.2, C7.2, C8.2, C9.2, C10.2, C12.2, C14.2, C15.2, IC1.1 (1A), IC1.2 (1B), IC1.7 (GND), IC2.3 (GND), IC4.2 (1D), IC4.7 (GND), IC4.11 (2CP), IC4.12 (2D), IC4.13 (~2RD), IC5.2 (GND), IC6.4 (2A), IC6.5 (2B), IC6.7 (GND), IC7.7 (GND), IC8.7 (GND), IC9.7 (A5), IC9.10 (GND), IC10.4 (GND), IC11.7 (GND), IC13.7 (GND), J2.5, J2.12, J2.21, J2.28
MPU0: IC9.8 (A6), J2.7
MPU1: IC9.9 (A7), J2.6
NMI Enabled: IC4.6 (~1Q), IC9.6 (A4), J2.24
Set Disable NMI: IC6.13 (4B), J2.27
Set Enable NMI: IC6.10 (3B), J2.26
~NMI State: IC6.1 (1A), IC9.1 (~OE1), J2.23
~NMI: IC2.4 (Y), J2.32
~RD: IC9.19 (~OE2), J2.3
~Reset: IC7.3 (2A), J2.2
~Set Break_{1}: IC7.13 (6A), J2.29
~Set Break_{2}: IC7.9 (4A), J2.30
~Set Break_{3}: IC7.11 (5A), J2.31
~Set Timer: IC7.1 (1A), J2.25
~WD: IC6.2 (1B), J2.4

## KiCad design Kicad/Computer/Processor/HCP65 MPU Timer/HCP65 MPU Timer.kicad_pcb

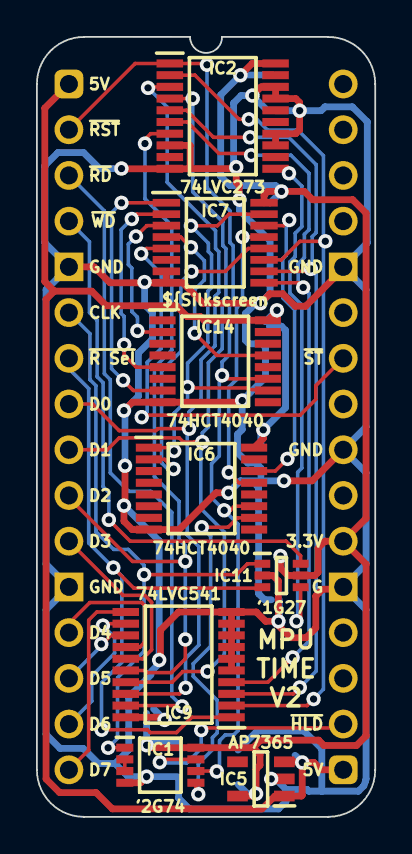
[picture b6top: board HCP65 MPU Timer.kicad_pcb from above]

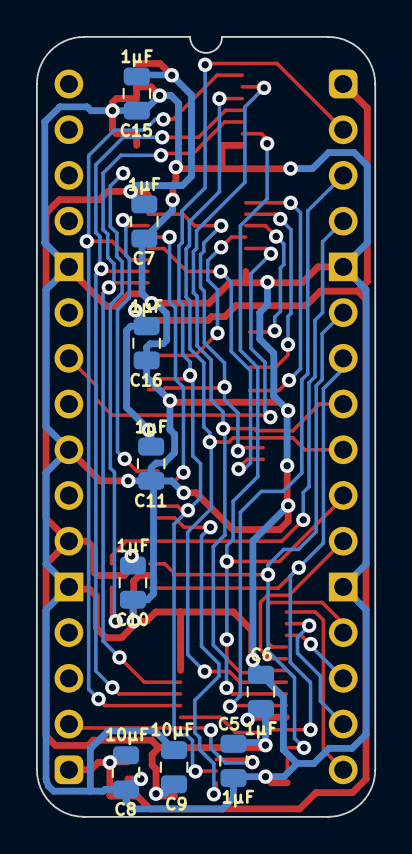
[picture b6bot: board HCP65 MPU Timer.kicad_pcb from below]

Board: 2 copper layers, 18.8 x 43.3 mm, 18 parts (9 on the bottom side), 32 nets.

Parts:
C5, C6, C7, C10, C11, C15, C16: 1μF; C_0805
C8, C9: 10µF; C_0805
IC1: 74LVC2G74DP,125; SOP65P400X110-8N
IC2: 74LVC273PW,118; SOP65P640X110-20N
IC5: AP7365-33WG-7; SOT95P285X130-5N
IC6, IC14: 74HCT4040PW,118; SOP65P640X110-16N
IC7: PI3B3251QE; SOP64P599X175-16N
IC9: 74LVC541APW,118; SOP65P640X110-20N
IC11: 74LVC1G27GW,125; SOP65P210X110-6N
J2: Board 2x16 W15.24mm; DIP-32_Board_W15.24mm

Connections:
3.3V: C5.1, C6.1, C7.1, C9.1, C10.1, C15.1, IC1.8 (3V), IC2.20 (3V), IC5.5 (3.3VOut), IC7.16 (3V), IC9.20 (3V), IC11.5 (3V), J2.22
5V: C8.1, C11.1, C16.1, IC5.1 (6VIn), IC5.3 (EN), IC6.16 (5V), IC14.16 (5V), J2.1, J2.17
/NMI_{Speed}0: IC2.2 (Q0), IC7.11 (S0), IC9.2 (A0)
/NMI_{Speed}1: IC2.5 (Q1), IC7.10 (S1), IC9.3 (A1)
/NMI_{Speed}2: IC2.6 (Q2), IC7.9 (S2), IC9.4 (A2)
/Q0: IC1.5 (Q), IC6.10 (~CP)
/Q6: IC6.2 (Q5), IC7.12 (I7)
/Q8: IC6.13 (Q7), IC7.13 (I6)
/Q10: IC6.14 (Q9), IC7.14 (I5)
/Q12: IC6.1 (Q11), IC7.15 (I4), IC14.10 (~CP)
/Q14: IC7.1 (I3), IC14.7 (Q1)
/Q16: IC7.2 (I2), IC14.5 (Q3)
/Q18: IC7.3 (I1), IC14.2 (Q5)
/Q20: IC7.4 (I0), IC14.13 (Q7)
/~Q: IC1.2 (D), IC1.3 (~Q)
/~Write NMI Rate Select·CLK: IC2.11 (CP), IC11.4 (Y)
CLK: IC1.1 (CP), IC11.1 (A), J2.6
D0: IC2.3 (D0), IC9.18 (Y0), J2.8
D1: IC2.4 (D1), IC9.17 (Y1), J2.9
D2: IC2.7 (D2), IC9.16 (Y2), J2.10
D3: IC9.15 (Y3), J2.11
D4: IC9.14 (Y4), J2.13
D5: IC9.13 (Y5), J2.14
D6: IC9.12 (Y6), J2.15
D7: IC9.11 (Y7), J2.16
GND: C5.2, C6.2, C7.2, C8.2, C9.2, C10.2, C11.2, C15.2, C16.2, IC1.4 (GND), IC2.8 (D3), IC2.10 (GND), IC2.13 (D4), IC2.14 (D5), IC2.17 (D6), IC2.18 (D7), IC5.2 (GND), IC6.8 (GND), IC7.7 (~OE), IC7.8 (GND), IC9.5 (A3), IC9.6 (A4), IC9.7 (A5), IC9.8 (A6), IC9.9 (A7), IC9.10 (GND), IC11.2 (GND), IC14.8 (GND), J2.5, J2.12, J2.21, J2.24, J2.28
~Hold: IC1.7 (~SD), J2.18
~NMI Rate Select: IC9.1 (~OE1), IC11.3 (B), J2.7
~RD: IC9.19 (~OE2), J2.3
~Reset: IC1.6 (~RD), IC2.1 (~MR), IC6.11 (MR), IC14.11 (MR), J2.2
~Set Timer: IC7.5 (Y), J2.26
~WD: IC11.6 (C), J2.4
